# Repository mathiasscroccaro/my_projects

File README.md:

# Projetos pessoais meus

## 7segmentos

In this directory you'll find a 7 segments led controller that was developed for my laboratory display

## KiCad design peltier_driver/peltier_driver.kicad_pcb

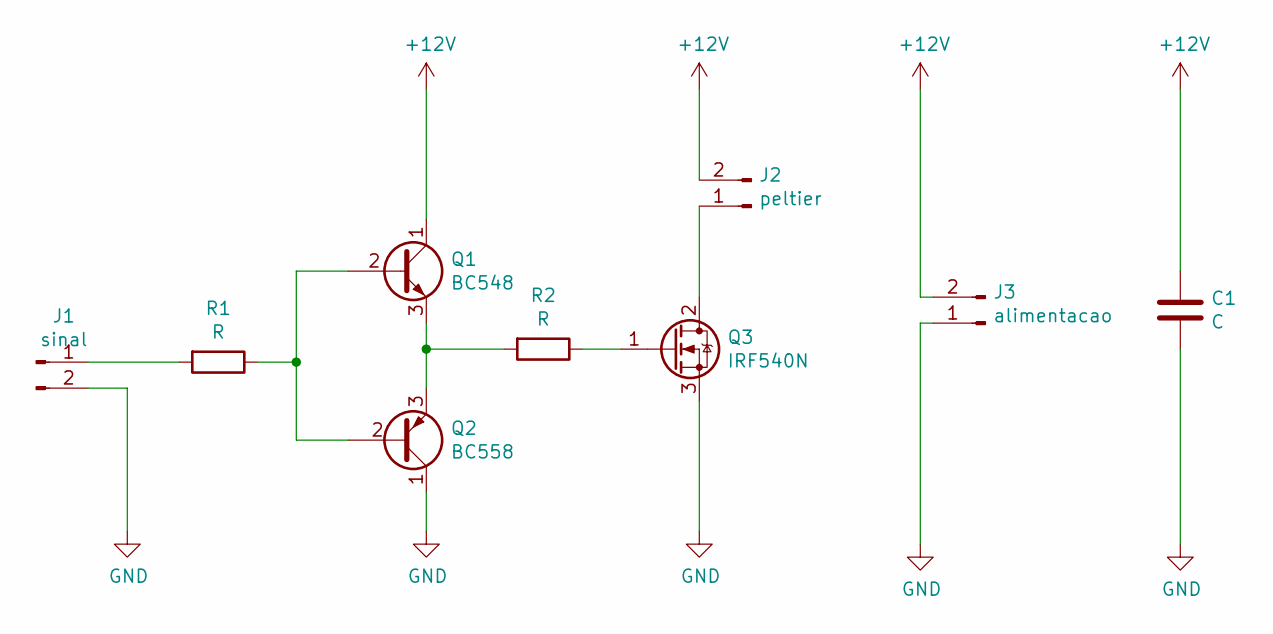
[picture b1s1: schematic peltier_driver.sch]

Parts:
C1: C; CP_Radial_D8.0mm_P3.50mm
J1: sinal; PinHeader_1x02_P2.54mm_Vertical
J2: peltier; TerminalBlock_Altech_AK300-2_P5.00mm
J3: alimentacao; TerminalBlock_Altech_AK300-2_P5.00mm
Q1: BC548; TO-92_Inline
Q2: BC558; TO-92_Inline
Q3: IRF540N; TO-220-3_Vertical
R1, R2: R; R_Axial_DIN0309_L9.0mm_D3.2mm_P12.70mm_Horizontal

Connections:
+12V: C1.1, J2.2, J3.2, Q1.1 (C)
GND: C1.2, J1.2, J3.1, Q2.1 (C), Q3.3 (S)
unnamed: J1.1, R1.2
unnamed: J2.1, Q3.2 (D)
unnamed: Q1.2 (B), Q2.2 (B), R1.1
unnamed: Q1.3 (E), Q2.3 (E), R2.2
unnamed: Q3.1 (G), R2.1

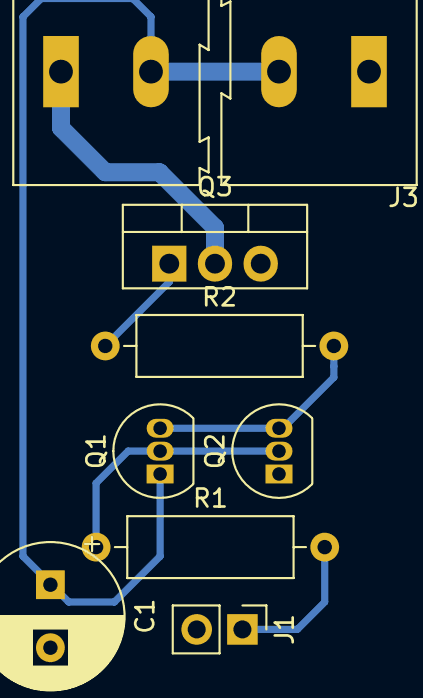
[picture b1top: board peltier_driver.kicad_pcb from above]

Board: 2 copper layers, 9 parts (0 on the bottom side), 7 nets.

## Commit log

2019-02-03 first
2019-02-03 Desenvolvendo o esquemático
2019-03-08 peltier driver
